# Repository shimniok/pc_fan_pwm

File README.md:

# pc_fan_pwm
Simple PWM control for PC fan

A simple pwm controller for PC fans using ATtiny1624, 2N7000 MOSFET, and potentiometer for speed adjustment.

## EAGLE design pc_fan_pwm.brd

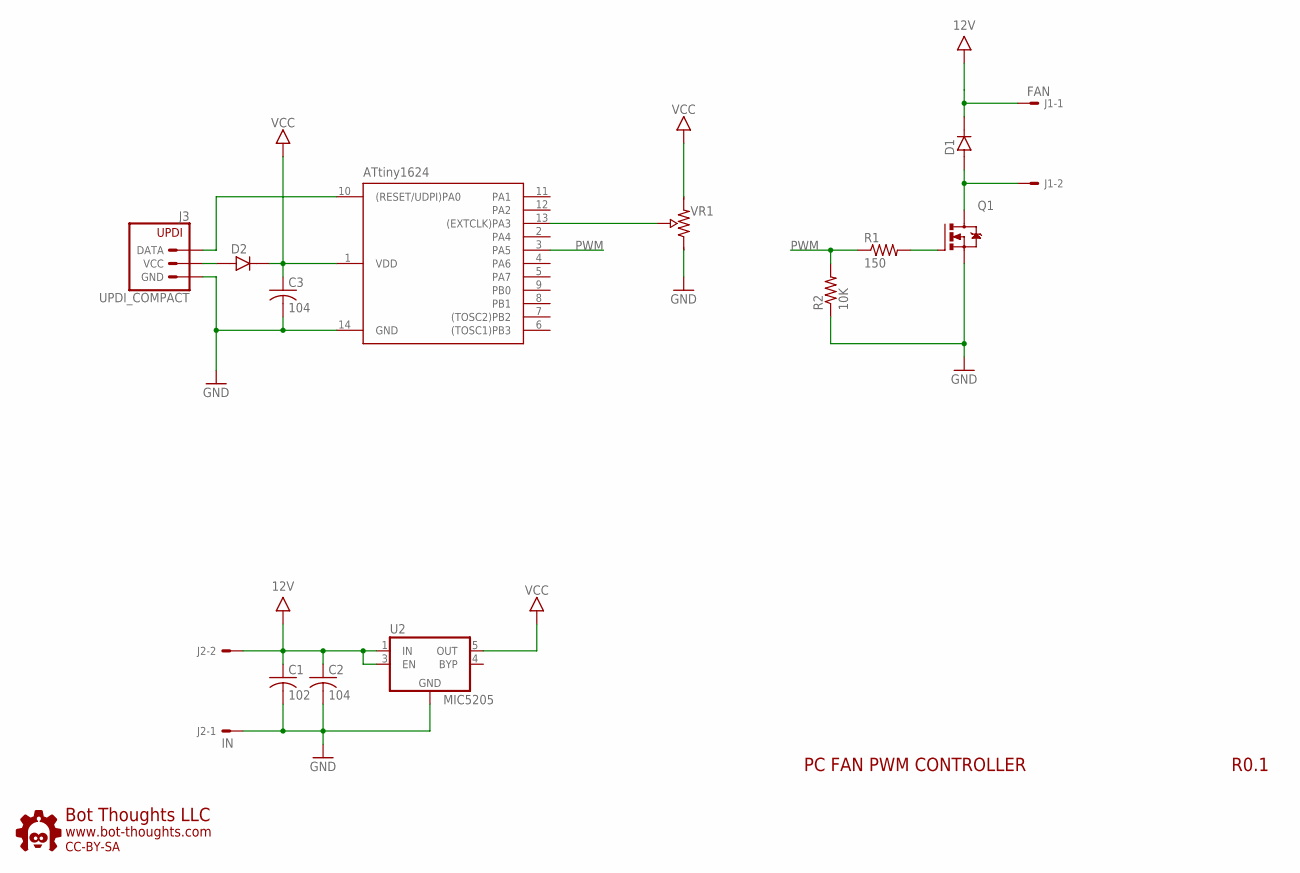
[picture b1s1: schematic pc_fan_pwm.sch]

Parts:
C1: 102; 0603
C2, C3: 104; 0603
D1, D2: DIODE_SOD323; SOD-323
J1: FAN; 7395-03
J2: IN; 7395-03
J3: UPDI_COMPACT; UPDI_1X3
Q1: 2N7000; TO92D-
R1: 150; 0603
R2: 10K; 0603
U1: ATTINY1624-SSU; SOIC14N
U2: MIC5205; SOT23-5
U$6: BTLOGO-LOGO-SM; BTLOGOS
VR1: TRIM-2X2.5; POT_0.2X0.25

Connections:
12V: C1.1 (+), C2.1 (+), J2.2, U2.1 (IN), U2.3 (EN)
FAN+: D1.C, J1.1
GND: C1.2 (-), C2.2 (-), C3.2 (-), J2.1, J3.2 (GND), Q1.1 (S), R2.1, U1.14 (GND), U2.2 (GND), VR1.A
unnamed: Q1.2 (G), R1.2
unnamed: U1.13 ((EXTCLK)PA3), VR1.W (WIPER)
unnamed: D1.A, J1.2, Q1.3 (D)
unnamed: J3.3 (DATA), U1.10 ((RESET/UDPI)PA0)
PWM: R1.1, R2.2, U1.3 (PA5)
VCC: C3.1 (+), D2.C, U1.1 (VDD), U2.5 (OUT), VR1.B
VIN: D2.A, J3.1 (VCC)

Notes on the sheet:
PC FAN PWM CONTROLLER
R0.1

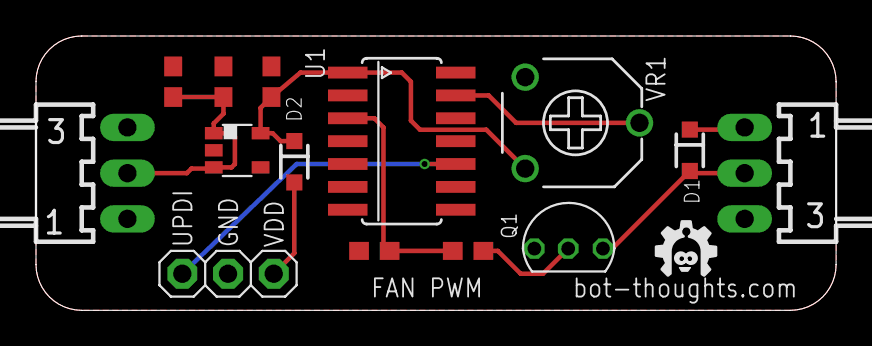
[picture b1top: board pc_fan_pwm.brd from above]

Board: 2 copper layers, 44.5 x 15.2 mm, 15 parts (0 on the bottom side), 10 nets.

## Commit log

2023-08-18 Create README.md
    Added readme
2023-08-18 initial version

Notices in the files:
parts and their libraries:
bt: CC-BY-SA
